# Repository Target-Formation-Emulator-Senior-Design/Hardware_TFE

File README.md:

# Hardware_TFE
KiCAD PCB and System Case Design

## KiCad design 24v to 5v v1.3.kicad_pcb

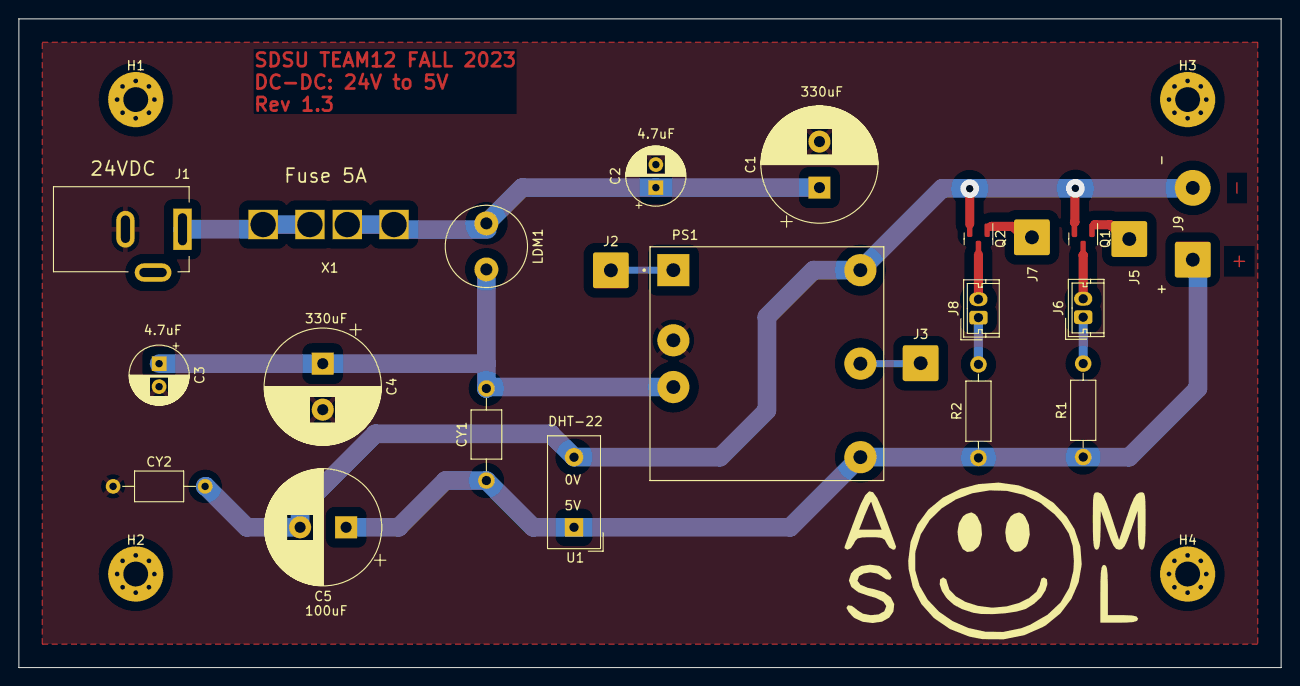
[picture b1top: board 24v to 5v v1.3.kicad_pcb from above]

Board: 2 copper layers, 137.2 x 70.5 mm, 27 parts (0 on the bottom side), 14 nets.

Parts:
C1, C4: 330u; CP_Radial_D12.5mm_P5.00mm
C2, C3: 4.7u; CP_Radial_D6.3mm_P2.50mm
C5: 100u; CP_Radial_D12.5mm_P5.00mm
CY1, CY2: 1n; C_Axial_L5.1mm_D3.1mm_P10.00mm_Horizontal
H1, H2, H3, H4: MountingHole; MountingHole_2.7mm_Pad_Via
J1: Conn_01x01; BarrelJack_Kycon_KLDX-0202-xC_Horizontal
J2, J3, J5, J7: Conn_01x01; SolderWire-2sqmm_1x01_D2mm_OD3.9mm
J6, J8: Conn_01x02; Molex_Micro-Latch_53253-0270_1x02_P2.00mm_Vertical
J9: Conn_01x01; SolderWire-2sqmm_1x02_P7.8mm_D2mm_OD3.9mm
LDM1: 2.2u; L_Radial_D8.7mm_P5.00mm_Fastron_07HCP
PS1: PDQE20-Q24-S5-D; CONV_PDQE20-Q24-S5-D
Q1, Q2: NMOS; SOT-23
R1, R2: 5.6; R_Axial_DIN0207_L6.3mm_D2.5mm_P10.16mm_Horizontal
U1: DHT22; Aosong_DHT11_5.5x12.0_P2.54mm
X1: 3522-2; FUSE_3522-2

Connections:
/5V: C5.1, CY1.1, J9.1, PS1.4 (+VO), R1.1, R2.1, U1.1 (VCC)
/24V: J1.1, X1.2A, X1.2B
GND: C1.2, C2.2, C3.2, C4.2, CY2.1, J1.2, PS1.2 (GND)
unnamed: C1.1, C2.1, LDM1.1, X1.1A, X1.1B
unnamed: J2.1, PS1.1 (CTRL)
unnamed: J3.1, PS1.5 (TRIM)
unnamed: J5.1, Q1.1 (D)
unnamed: J6.1, R1.2
unnamed: J6.2, Q1.3 (S)
unnamed: J7.1, Q2.1 (D)
unnamed: J8.1, R2.2
unnamed: J8.2, Q2.3 (S)
unnamed: C5.2, CY2.2, J9.2, PS1.6 (0V), Q1.2 (G), Q2.2 (G), U1.4 (GND)
unnamed: C3.1, C4.1, CY1.2, LDM1.2, PS1.3 (VIN)

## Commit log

2023-09-15 KiCAD Schematic 24V buck converter
    24Vin to 5V@3A and 5V@2A. This schematic is not complete.
2023-09-22 24V to 5V 4A single output CUI switch
    Need footprints for caps, inductor, connectors etc
2023-09-22 24V buck converter CUI switch
    Needs footprint for pcb portion. Updated input VCC on DHT22 from power input to input. CHeck on ground coming from 0V output at switcher. Does not pass ERC.
2023-11-17 24V to 5V KiCAD files version 1.1
    KiCAD files for 24V to 5V buck converter.
    1. Increased trace width edge gap to avoid shorts.
    2. Larger footprint for fuse
    3. Removed silkscreen outline for 5A fuse, this avoids screen printing on pads
2023-11-17 24v to 5v v1.3
    Increased LED pad sizes
    Increased both via size to 2.03
    Moved GPIO gate pin to otherside of power trace to avoid signal issues
    Rearranges some silkscreen text
2023-12-21 Delete 24v to 5v oct prototype v1.1 directory
    Obsolete
2023-12-21 Delete 24V buck converter V4.kicad_sch
    Obsolete
2023-12-21 Delete 24V buck converter V5.kicad_sch
    Obsolete
2023-12-21 Delete 24V buck converter dual output V2.kicad_sch
    Obsolete
2023-12-21 Delete 24V stepdown circuit.kicad_sch
    Obsolete
2023-12-21 Delete 24V to 5V stepdown circuit.kicad_pcb
    Obsolete
2023-12-21 Gerber files
    Compressed gerber files from 24V to 5V converter version 1.3
    Generated in KiCAD V7
2023-12-22 TFE Instructions for use
    Instructions for Hardware, Firmware and Software
    Information for capabilities and device use
